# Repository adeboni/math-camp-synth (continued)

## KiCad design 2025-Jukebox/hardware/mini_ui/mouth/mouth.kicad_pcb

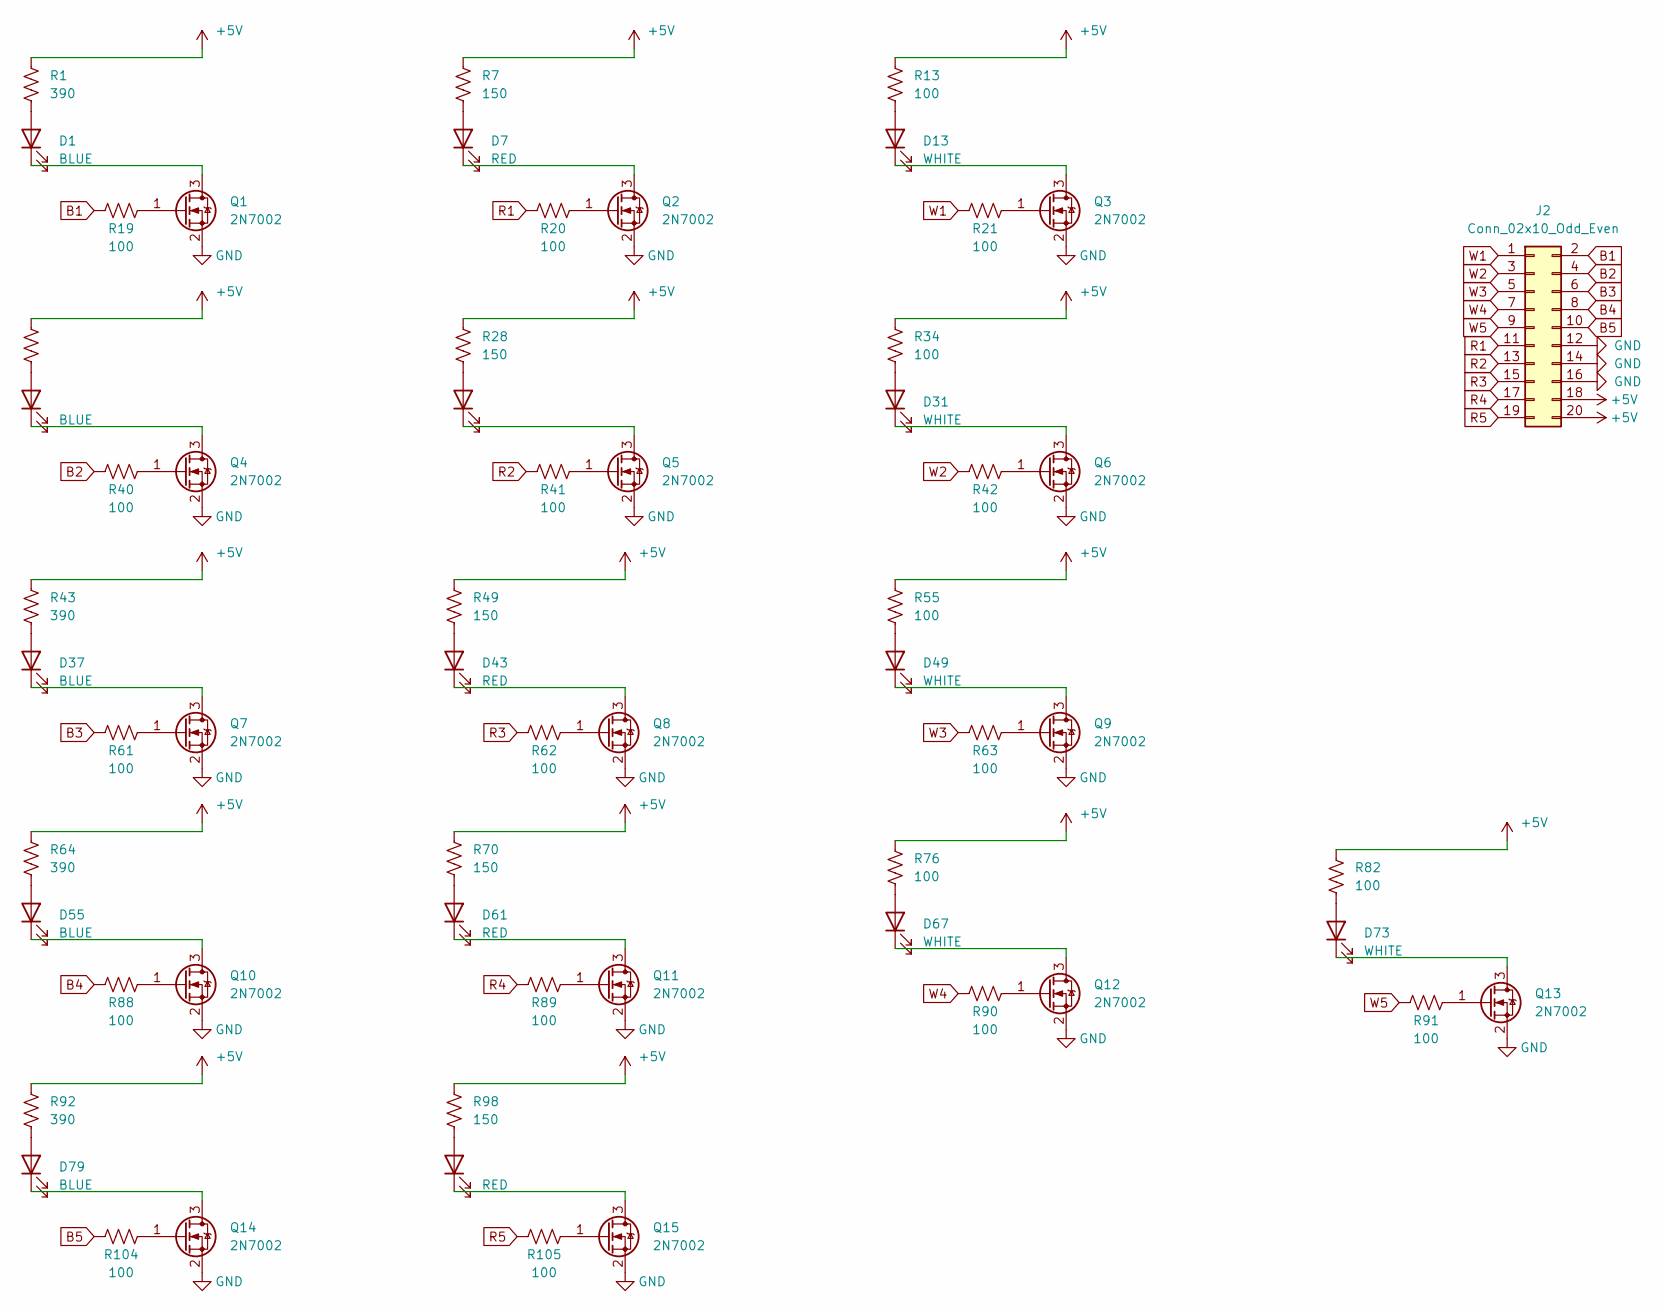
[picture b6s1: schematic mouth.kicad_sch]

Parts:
D1, D19, D37, D55, D79: BLUE; LED_0603_1608Metric
D7, D25, D43, D61, D85: RED; LED_0603_1608Metric
D13, D31, D49, D67, D73: WHITE; LED_0603_1608Metric
J2: Conn_02x10_Odd_Even; PinSocket_2x10_P2.54mm_Vertical_SMD
Q1, Q2, Q3, Q4, Q5, Q6, Q7, Q8, Q9, Q10, Q11, Q12, Q13, Q14, Q15: 2N7002; SOT-23
R1, R22, R43, R64, R92: 390; R_0603_1608Metric
R7, R28, R49, R70, R98: 150; R_0603_1608Metric
R13, R19, R20, R21, R34, R40, R41, R42, R55, R61, R62, R63, R76, R82, R88, R89, R90, R91, R104, R105: 100; R_0603_1608Metric

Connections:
+5V: J2.18, J2.20, R1.2, R7.2, R13.2, R22.2, R28.2, R34.2, R43.2, R49.2, R55.2, R64.2, R70.2, R76.2, R82.2, R92.2, R98.2
B1: J2.2, R19.1
B2: J2.4, R40.1
B3: J2.6, R61.1
B4: J2.8, R88.1
B5: J2.10, R104.1
GND: J2.12, J2.14, J2.16, Q1.2 (S), Q2.2 (S), Q3.2 (S), Q4.2 (S), Q5.2 (S), Q6.2 (S), Q7.2 (S), Q8.2 (S), Q9.2 (S), Q10.2 (S), Q11.2 (S), Q12.2 (S), Q13.2 (S), Q14.2 (S), Q15.2 (S)
unnamed: D1.2 (A), R1.1
unnamed: D1.1 (K), Q1.3 (D)
unnamed: D7.2 (A), R7.1
unnamed: D7.1 (K), Q2.3 (D)
unnamed: D13.2 (A), R13.1
unnamed: D13.1 (K), Q3.3 (D)
unnamed: D19.2 (A), R22.1
unnamed: D19.1 (K), Q4.3 (D)
unnamed: D25.2 (A), R28.1
unnamed: D25.1 (K), Q5.3 (D)
unnamed: D31.2 (A), R34.1
unnamed: D31.1 (K), Q6.3 (D)
unnamed: D37.2 (A), R43.1
unnamed: D37.1 (K), Q7.3 (D)
unnamed: D43.2 (A), R49.1
unnamed: D43.1 (K), Q8.3 (D)
unnamed: D49.2 (A), R55.1
unnamed: D49.1 (K), Q9.3 (D)
unnamed: D55.2 (A), R64.1
unnamed: D55.1 (K), Q10.3 (D)
unnamed: D61.2 (A), R70.1
unnamed: D61.1 (K), Q11.3 (D)
unnamed: D67.2 (A), R76.1
unnamed: D67.1 (K), Q12.3 (D)
unnamed: D73.2 (A), R82.1
unnamed: D73.1 (K), Q13.3 (D)
unnamed: D79.2 (A), R92.1
unnamed: D79.1 (K), Q14.3 (D)
unnamed: D85.2 (A), R98.1
unnamed: D85.1 (K), Q15.3 (D)
unnamed: Q1.1 (G), R19.2
unnamed: Q2.1 (G), R20.2
unnamed: Q3.1 (G), R21.2
unnamed: Q4.1 (G), R40.2
unnamed: Q5.1 (G), R41.2
unnamed: Q6.1 (G), R42.2
unnamed: Q7.1 (G), R61.2
unnamed: Q8.1 (G), R62.2
unnamed: Q9.1 (G), R63.2
unnamed: Q10.1 (G), R88.2
unnamed: Q11.1 (G), R89.2
unnamed: Q12.1 (G), R90.2
unnamed: Q13.1 (G), R91.2
unnamed: Q14.1 (G), R104.2
unnamed: Q15.1 (G), R105.2
R1: J2.11, R20.1
R2: J2.13, R41.1
R3: J2.15, R62.1
R4: J2.17, R89.1
R5: J2.19, R105.1
W1: J2.1, R21.1
W2: J2.3, R42.1
W3: J2.5, R63.1
W4: J2.7, R90.1
W5: J2.9, R91.1

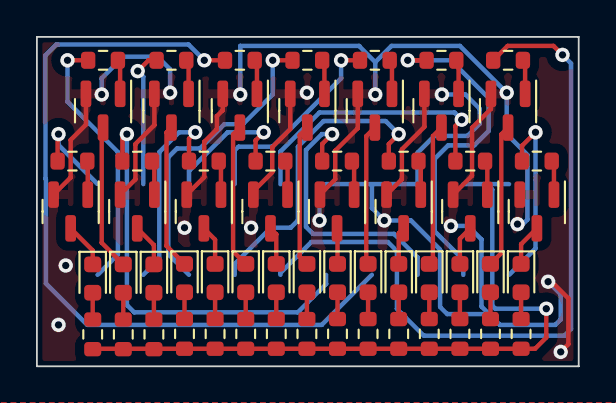
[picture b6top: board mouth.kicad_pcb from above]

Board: 2 copper layers, 30.1 x 18.3 mm, 61 parts (1 on the bottom side), 62 nets.

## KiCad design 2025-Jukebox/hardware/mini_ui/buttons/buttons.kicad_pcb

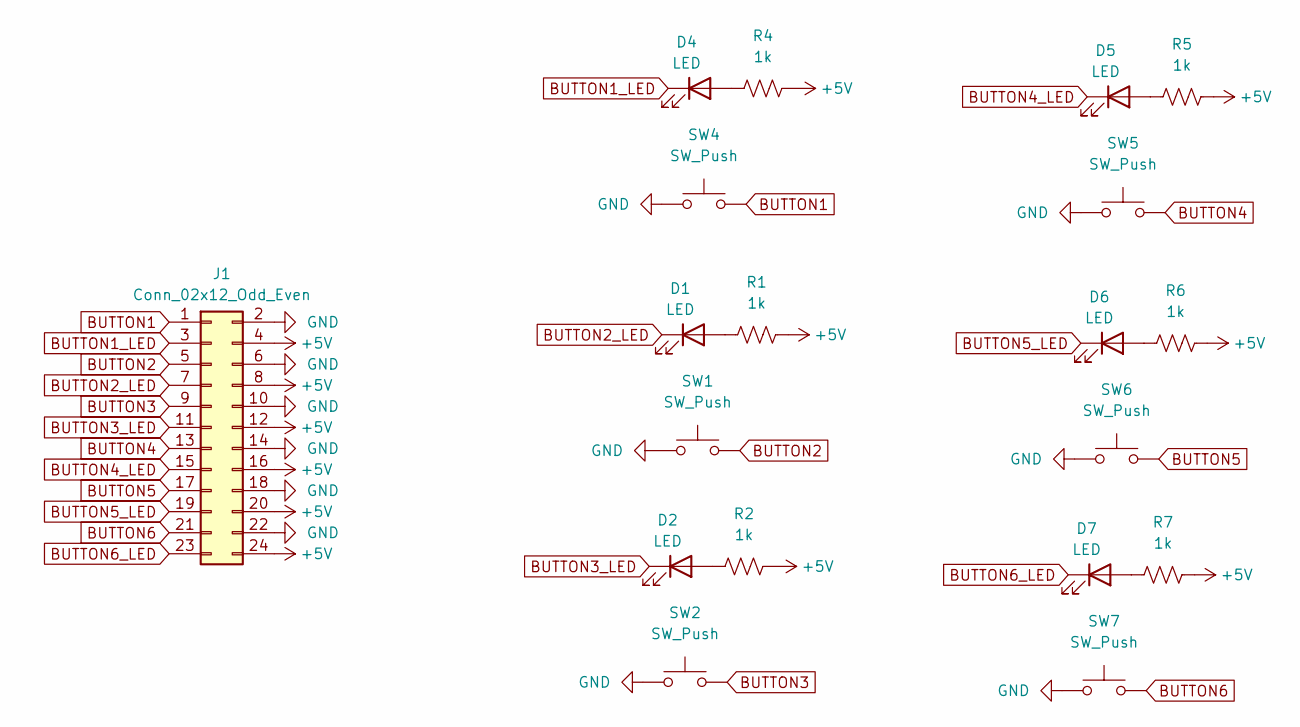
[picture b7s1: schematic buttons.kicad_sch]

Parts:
D1, D2, D4, D5, D6, D7: LED; LED_0603_1608Metric
J1: Conn_02x12_Odd_Even; PinSocket_2x12_P2.54mm_Vertical_SMD
R1, R2, R4, R5, R6, R7: 1k; R_0603_1608Metric
SW1, SW2, SW4, SW5, SW6, SW7: SW_Push; SW_Push_SPST_NO_Alps_SKRK

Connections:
+5V: J1.4, J1.8, J1.12, J1.16, J1.20, J1.24, R1.2, R2.2, R4.2, R5.2, R6.2, R7.2
BUTTON1: J1.1, SW4.2
BUTTON1_LED: D4.1 (K), J1.3
BUTTON2: J1.5, SW1.2
BUTTON2_LED: D1.1 (K), J1.7
BUTTON3: J1.9, SW2.2
BUTTON3_LED: D2.1 (K), J1.11
BUTTON4: J1.13, SW5.2
BUTTON4_LED: D5.1 (K), J1.15
BUTTON5: J1.17, SW6.2
BUTTON5_LED: D6.1 (K), J1.19
BUTTON6: J1.21, SW7.2
BUTTON6_LED: D7.1 (K), J1.23
GND: J1.2, J1.6, J1.10, J1.14, J1.18, J1.22, SW1.1, SW2.1, SW4.1, SW5.1, SW6.1, SW7.1
unnamed: D1.2 (A), R1.1
unnamed: D2.2 (A), R2.1
unnamed: D4.2 (A), R4.1
unnamed: D5.2 (A), R5.1
unnamed: D6.2 (A), R6.1
unnamed: D7.2 (A), R7.1

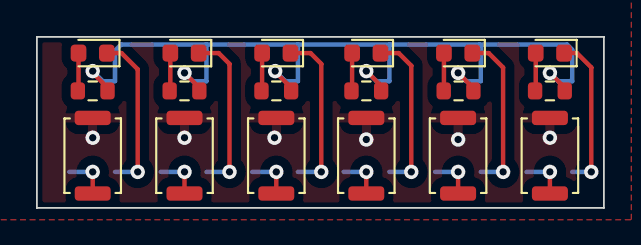
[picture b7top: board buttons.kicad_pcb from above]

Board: 2 copper layers, 31.5 x 9.5 mm, 19 parts (1 on the bottom side), 20 nets.

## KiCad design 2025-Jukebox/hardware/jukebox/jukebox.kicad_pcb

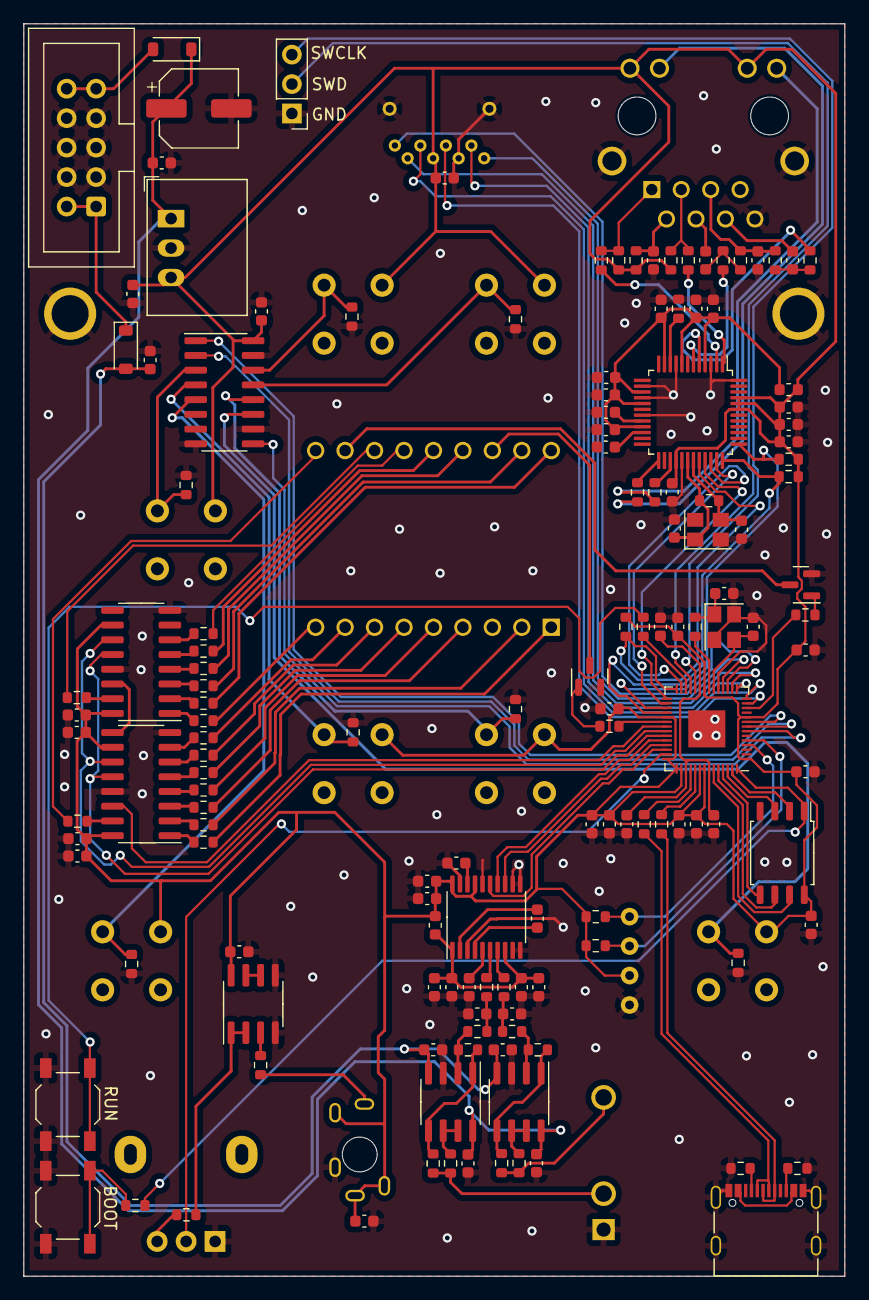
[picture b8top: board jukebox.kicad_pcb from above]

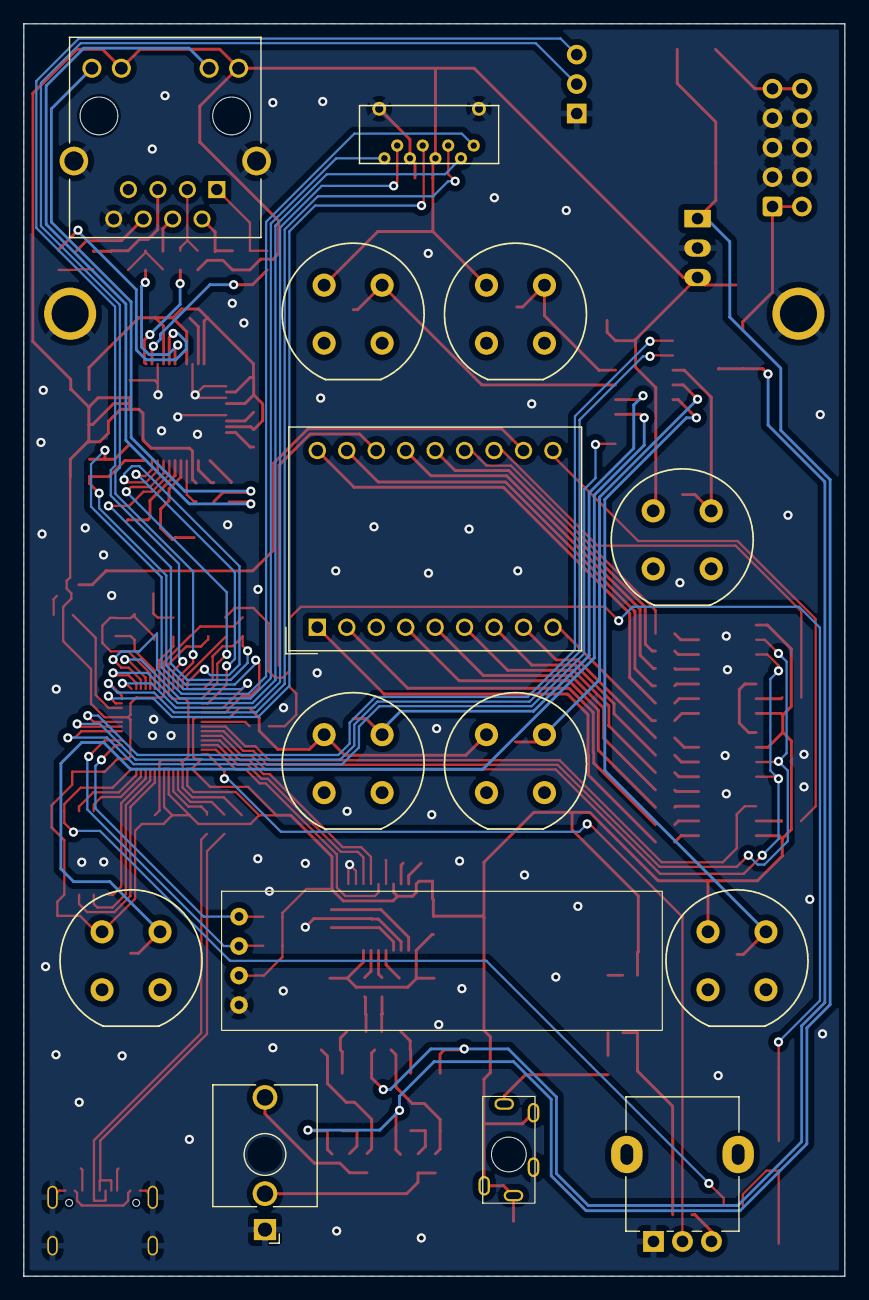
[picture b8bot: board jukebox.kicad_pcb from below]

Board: 2 copper layers, 70.8 x 108.0 mm, 160 parts (14 on the bottom side), 140 nets.

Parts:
C1, C2, C3, C4, C5, C6, C7, C8, C9, C13, C14, C15, C16, C17, C18, C19, C20, C21, C22, C23, C27, C31, C38, C40, C45, C46, C53, C54, C55, C56, C57, C59: 100n; C_0603_1608Metric
C10, C11, C44: 1u; C_0603_1608Metric
C12, C30, C36, C37, C39, C41, C42, C47, C48, C52, C58: 10u; C_0603_1608Metric
C24, C28: 27p; C_0603_1608Metric
C25, C29: 22p; C_0603_1608Metric
C26, C32: 10n; C_0603_1608Metric
C33, C34: 6.8n; C_0603_1608Metric
C35: 100u; CP_Elec_6.3x5.4
C43, C49: 2.2u; C_0603_1608Metric
C50, C51: 2.2n; C_0603_1608Metric
D1, D2: SM4007; D_SOD-123
FB1, FB3: FerriteBead; L_0603_1608Metric
H1, H2: MountingHole_Pad; MountingHole_3.2mm_M3_DIN965_Pad
J1: AudioJack3_SwitchTR; STX-3790-5N
J2: USB_C_Receptacle_USB2.0; USB_C_Receptacle_Palconn_UTC16-G
J3: AudioJack2_SwitchT; Jack_3.5mm_QingPu_WQP-PJ398SM_Vertical_CircularHoles
J4: SI-46001-F; BEL_SI-46001-F
J5: Conn_01x04; SSD1306
J6: Conn_02x05_Odd_Even; IDC-Header_2x05_P2.54mm_Vertical
J7: Conn_01x03; PinHeader_1x03_P2.54mm_Vertical
Q1, Q2: MMBT3904; SOT-23
R1, R2, R24, R25, R38: 1k; R_0603_1608Metric
R3, R6, R13, R17, R18, R28, R31, R32, R33, R35, R36, R37, R39, R40, R41, R58: 100; R_0603_1608Metric
R4, R5: 27; R_0603_1608Metric
R7, R10, R59, R61: 5.1k; R_0603_1608Metric
R8, R14, R16, R43, R44, R45, R46, R47, R48, R49, R50, R51, R54, R55: 10k; R_0603_1608Metric
R9, R11, R12, R15: 4.7; R_0603_1608Metric
R19, R20, R21, R22: 49.9; R_0603_1608Metric
R23: 1M; R_0603_1608Metric
R26, R27, R34, R42: 470; R_0603_1608Metric
R29: 12.4k; R_0603_1608Metric
R30: 10; R_0603_1608Metric
R52, R53, R56, R57: 75; R_0603_1608Metric
R60: 100k; R_0603_1608Metric
RV1: 100k; Potentiometer_Alpha_RD901F-40-00D_Single_Vertical
SW1, SW2: SW_Push; SW_SPST_TL3342
SW3, SW4, SW5, SW6, SW7, SW8, SW9: SW_Push; Push_E-Switch_KS01Q01
U1: PCM5100A; TSSOP-20_4.4x6.5mm_P0.65mm
U2: RP2040; QFN-56-1EP_7x7mm_P0.4mm_EP3.2x3.2mm
U3: W5500; LQFP-48_7x7mm_P0.5mm
U4: PDC54-11GWA; DA56-11CGKWA
U5, U8: 74HC595; SOIC-16_3.9x9.9mm_P1.27mm
U6: R-783.3-1.0; Converter_DCDC_RECOM_R-78E-0.5_THT
U7: W25Q128JVS; SOIC-8_5.23x5.23mm_P1.27mm
U9: PJS008U-3000-0
U10, U11: NE5532; SOIC-8_3.9x4.9mm_P1.27mm
U12: MCP6002-xSN; SOIC-8_3.9x4.9mm_P1.27mm
U13: 74HC165; SOIC-16_3.9x9.9mm_P1.27mm
Y1: 12MHz; Crystal_SMD_3225-4Pin_3.2x2.5mm
Y2: 25MHz; Crystal_SMD_3225-4Pin_3.2x2.5mm

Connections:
+1V1: C1.1, C2.1, C10.1, U2.23 (DVDD), U2.45 (VREG_VOUT), U2.50 (DVDD)
+3.3V: C3.1, C4.1, C5.1, C6.1, C7.1, C8.1, C9.1, C11.1, C12.1, C13.1, C14.1, C15.1, C16.1, C23.1, C27.1, C36.1, C37.1, C38.1, C39.1, C40.1, C42.1, C57.1, C58.1, C59.1, FB1.1, FB3.1, J1.R, J1.RN, J1.TN, J4.10, J4.12, J5.3, R8.1, R14.1, R16.1, R19.2, R20.2, R30.2, R59.2, R61.2, SW3.1, SW4.1, SW5.1, SW6.1, SW7.1, SW8.1, SW9.1, U1.17 (XSMT), U1.20 (DVDD), U2.1 (IOVDD), U2.10 (IOVDD), U2.22 (IOVDD), U2.33 (IOVDD), U2.42 (IOVDD), U2.43 (ADC_AVDD), U2.44 (VREG_IN), U2.48 (USB_VDD), U2.49 (IOVDD), U3.28 (VDD), U3.43 (PMODE2), U3.44 (PMODE1), U3.45 (PMODE0), U5.10 (~SRCLR), U5.16 (VCC), U6.3 (OUT), U7.8 (VCC), U8.10 (~SRCLR), U8.16 (VCC), U9.P$4 (4_VDD), U12.8 (V+), U13.16 (VCC)
+3.3VA: C17.1, C18.1, C19.1, C20.1, C21.1, C22.1, FB1.2, U3.4 (AVDD), U3.8 (AVDD), U3.11 (AVDD), U3.15 (AVDD), U3.17 (AVDD), U3.21 (AVDD)
+12V: C35.1, C41.1, C53.1, C55.1, D2.1 (K), U6.1 (IN), U10.8 (V+), U11.8 (V+)
-12V: C52.1, C54.2, C56.2, D1.2 (A), U10.4 (V-), U11.4 (V-)
/CS_0: R8.2, U2.28 (GPIO17), U3.32 (~SCS)
/INTn: R14.2, U2.32 (GPIO21), U3.36 (~INT)
/MISO_0: U2.27 (GPIO16), U3.34 (MISO)
/MOSI_0: U2.30 (GPIO19), U3.35 (MOSI)
/QSPI_SCLK: U2.52 (QSPI_SCLK), U7.6 (CLK)
/QSPI_SD0: U2.53 (QSPI_SD0), U7.5 (DI(IO0))
/QSPI_SD1: U2.55 (QSPI_SD1), U7.2 (DO(IO1))
/QSPI_SD2: U2.54 (QSPI_SD2), U7.3 (IO2)
/QSPI_SD3: U2.51 (QSPI_SD3), U7.7 (IO3)
/QSPI_SS: R38.1, U2.56 (QSPI_SS), U7.1 (~CS)
/RSTn: R16.2, U2.31 (GPIO20), U3.37 (~RST)
/RUN: R25.1, U2.26 (RUN)
/SCK_0: U2.29 (GPIO18), U3.33 (SCLK)
/~USB_BOOT: R38.2, SW2.2
ACTn: R27.1, U3.27 (ACTLED)
BCK_PWM1: U1.13 (BCK), U2.39 (GPIO27_ADC1)
BTN_CP: U2.8 (GPIO6), U13.2 (CP)
BTN_PL: U2.9 (GPIO7), U13.1 (~PL)
BTN_Q7: U2.7 (GPIO5), U13.9 (Q7)
D+: J2.A6 (D+), J2.B6 (D+), R4.1
D-: J2.A7 (D-), J2.B7 (D-), R5.1
GND: C1.2, C2.2, C3.2, C4.2, C5.2, C6.2, C7.2, C8.2, C9.2, C10.2, C11.2, C12.2, C13.2, C14.2, C15.2, C16.2, C17.2, C18.2, C19.2, C20.2, C21.2, C22.2, C23.2, C24.2, C25.1, C26.1, C27.2, C28.2, C29.2, C30.2, C31.2, C32.1, C35.2, C36.2, C37.2, C38.2, C39.2, C40.2, C41.2, C42.2, C44.2, C45.2, C46.2, C47.2, C48.2, C49.2, C50.2, C51.1, C52.2, C53.2, C54.1, C55.2, C56.1, C57.2, C58.2, C59.2, H1.1, H2.1, J1.S, J2.A1 (GND), J2.A12 (GND), J2.B1 (GND), J2.B12 (GND), J2.S1 (SHIELD), J3.S, J4.8, J4.SH, J5.4, J6.3, J6.4, J6.5, J6.6, J6.7, J6.8, J7.1, Q1.2 (E), Q2.2 (E), R7.1, R10.1, R29.1, R43.2, R44.2, R45.2, R46.2, R47.2, R48.2, R49.2, RV1.1, SW1.1, SW2.1, U1.3 (CPGND), U1.9 (AGND), U1.10 (DEMP), U1.11 (FLT), U1.12 (SCK), U1.16 (FMT), U1.19 (DGND), U2.19 (TESTEN), U2.57 (GND), U3.3 (AGND), U3.9 (AGND), U3.14 (AGND), U3.16 (AGND), U3.19 (AGND), U3.29 (GND), U3.48 (AGND), U5.8 (GND), U5.13 (~OE), U6.2 (GND), U7.4 (GND), U8.8 (GND), U8.13 (~OE), U9.P$6 (6_VSS/GND), U9.P$9 (HOUSING_1), U9.P$10 (HOUSING_2), U10.3 (+), U11.3 (+), U12.4 (V-), U12.5 (+), U13.8 (GND), U13.10 (DS), U13.15 (~CE), Y1.2, Y1.4, Y2.2, Y2.4
LINKn: R26.1, U3.25 (LINKLED)
LRCLK_PWM0: U1.15 (LRCK), U2.40 (GPIO28_ADC2)
NUM_A: R33.1, U4.12 (A)
NUM_B: R3.1, U4.10 (B)
NUM_C: R35.1, U4.9 (C)
NUM_D: R31.1, U4.7 (D)
NUM_DIG1: R1.2, U2.34 (GPIO22)
NUM_DIG2: R2.2, U2.12 (GPIO9)
NUM_DP: R32.1, U4.8 (DP)
NUM_E: R6.1, U4.1 (E)
NUM_EN: U2.37 (GPIO25), U5.12 (RCLK), U8.12 (RCLK)
NUM_F: R36.1, U4.18 (F)
NUM_G: R37.1, U4.17 (G)
NUM_H: R39.1, U4.15 (H)
NUM_J: R40.1, U4.14 (J)
NUM_K: R28.1, U4.6 (K)
NUM_L: R18.1, U4.5 (L)
NUM_M: R17.1, U4.4 (M)
NUM_N: R13.1, U4.2 (N)
NUM_P: R41.1, U4.13
NUM_SCK: U2.36 (GPIO24), U5.11 (SRCLK), U8.11 (SRCLK)
NUM_SER: U2.35 (GPIO23), U5.14 (SER)
unnamed: C28.1, R24.2, Y1.1
unnamed: C50.1, R42.2, R55.1
unnamed: C51.2, R34.2, R50.1
unnamed: D1.1 (K), J6.1, J6.2
unnamed: D2.2 (A), J6.9, J6.10
unnamed: J1.T, R60.1
unnamed: J2.A5 (CC1), R7.2
unnamed: J2.B5 (CC2), R10.2
unnamed: J2.A4 (VBUS), J2.A9 (VBUS), J2.B4 (VBUS), J2.B9 (VBUS)
unnamed: J3.T, R56.2, R57.2
unnamed: J3.TN, R52.2, R53.2
unnamed: J4.9, R27.2
unnamed: J4.11, R26.2
unnamed: C33.2, J4.4 (RD+)
unnamed: C34.1, J4.6 (RD-)
unnamed: C32.2, J4.2 (TCT), R30.1
unnamed: J7.2, U2.25 (SWD)
unnamed: J7.3, U2.24 (SWCLK)
unnamed: Q1.1 (B), R1.1
unnamed: Q1.3 (C), U4.16 (DIG_1)
unnamed: Q2.1 (B), R2.1
unnamed: Q2.3 (C), U4.11 (DIG_2)
unnamed: R25.2, SW1.2
unnamed: R58.2, RV1.3
unnamed: C43.2, U1.4 (CAPM)
unnamed: C43.1, U1.2 (CAPP)
unnamed: C44.1, U1.18 (LDOO)
unnamed: R34.1, U1.6 (OUTL)
unnamed: R42.1, U1.7 (OUTR)
unnamed: C49.1, U1.5 (VNEG)
unnamed: R5.2, U2.46 (USB_DM)
unnamed: R4.2, U2.47 (USB_DP)
unnamed: C24.1, U2.20 (XIN), Y1.3
unnamed: R24.1, U2.21 (XOUT)
unnamed: C31.1, U3.22 (1V2O)
unnamed: R29.2, U3.10 (EXRES1)
unnamed: R12.1, U3.5 (RXN)
unnamed: R15.2, U3.6 (RXP)
unnamed: C30.1, U3.20 (TOCAP)
unnamed: R9.1, U3.1 (TXN)
unnamed: R11.2, U3.2 (TXP)
unnamed: C25.2, R23.2, U3.30 (XI/CLKIN), Y2.1
unnamed: C29.1, R23.1, U3.31 (XO), Y2.3
unnamed: R3.2, U5.15 (QA)
unnamed: R6.2, U5.1 (QB)
unnamed: R13.2, U5.2 (QC)
unnamed: R17.2, U5.3 (QD)
unnamed: R18.2, U5.4 (QE)
unnamed: R28.2, U5.5 (QF)
unnamed: R31.2, U5.6 (QG)
unnamed: U5.9 (QH'), U8.14 (SER)
unnamed: R32.2, U5.7 (QH)
unnamed: R33.2, U8.15 (QA)
unnamed: R35.2, U8.1 (QB)
unnamed: R36.2, U8.2 (QC)
unnamed: R37.2, U8.3 (QD)
unnamed: R39.2, U8.4 (QE)
unnamed: R40.2, U8.5 (QF)
unnamed: R41.2, U8.6 (QG)
unnamed: R50.2, R51.1, U10.2 (-)
unnamed: R51.2, R53.1, U10.1, U10.5 (+)
unnamed: R52.1, U10.6 (-), U10.7
unnamed: R54.1, R55.2, U11.2 (-)
unnamed: R54.2, R57.1, U11.1, U11.5 (+)
unnamed: R56.1, U11.6 (-), U11.7
unnamed: R60.2, U12.3 (+)
unnamed: R58.1, U12.1, U12.2 (-)
unnamed: U12.6 (-), U12.7
unnamed: R49.1, SW3.2, U13.11 (D0)
unnamed: R48.1, SW6.2, U13.12 (D1)
unnamed: R47.1, SW4.2, U13.13 (D2)
unnamed: R46.1, SW5.2, U13.14 (D3)
unnamed: R45.1, SW8.2, U13.3 (D4)
unnamed: R44.1, SW7.2, U13.4 (D5)
unnamed: R43.1, SW9.2, U13.5 (D6)
PCM_DATA: U1.14 (DIN), U2.38 (GPIO26_ADC0)
RCT: C26.2, J4.5 (RCT), R21.2, R22.2
RXN: C34.2, R12.2, R21.1
RXP: C33.1, R15.1, R22.1
SCL: J5.2, R61.1, U2.5 (GPIO3)
SDA: J5.1, R59.1, U2.4 (GPIO2)
SD_CLK: U2.13 (GPIO10), U9.P$5 (5_CLK)
SD_CMD: U2.14 (GPIO11), U9.P$3 (3_CMD/DI)
SD_DAT0: U2.15 (GPIO12), U9.P$7 (7_DAT0/D0)
SD_DAT1: U2.18 (GPIO15), U9.P$8 (8_DAT1/X)
SD_DAT2: U2.17 (GPIO14), U9.P$1 (1_DAT2/X)
SD_DAT3: U2.16 (GPIO13), U9.P$2 (2_CD/DAT3/CS)
TXN: J4.3 (TD-), R9.2, R19.1
TXP: J4.1 (TD+), R11.1, R20.1
VOLUME: RV1.2, U2.41 (GPIO29_ADC3)
V_AUDIO: C45.1, C46.1, C47.1, C48.1, FB3.2, U1.1 (CPVDD), U1.8 (AVDD)

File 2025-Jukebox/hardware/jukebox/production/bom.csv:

Designator,Footprint,Quantity,Value,LCSC Part #
"C1, C13, C14, C15, C16, C17, C18, C19, C2, C20, C21, C22, C23, C27, C3, C31, C38, C4, C40, C45, C46, C5, C53, C54, C55, C56, C57, C59, C6, C7, C8, C9",0603,32,100n,C14663
"C10, C11, C44",0603,3,1u,C15849
"C12, C30, C36, C37, C39, C41, C42, C47, C48, C52, C58",0603,11,10u,C96446
"C24, C28",0603,2,27p,C1653
"C25, C29",0603,2,22p,C1653
"C26, C32",0603,2,10n,C57112
"C33, C34",0603,2,6.8n,C1631
C35,CP_Elec_6.3x5.4,1,100u,C180946
"C43, C49",0603,2,2.2u,C23630
"C50, C51",0603,2,2.2n,C1604
"D1, D2",D_SOD-123,2,SM4007,C64898
"FB1, FB3",0603,2,FerriteBead,C1002
J2,USB_C_Receptacle_Palconn_UTC16-G,1,USB_C_Receptacle_USB2.0,C709357
"Q1, Q2",SOT-23,2,MMBT3904,C20526
"R1, R2, R24, R25, R38",0603,5,1k,C21190
"R10, R59, R61, R7",0603,4,5.1k,C23186
"R11, R12, R15, R9",0603,4,4.7,C23164
"R13, R17, R18, R28, R3, R31, R32, R33, R35, R36, R37, R39, R40, R41, R58, R6",0603,16,100,C22775
"R14, R16, R43, R44, R45, R46, R47, R48, R49, R50, R51, R54, R55, R8",0603,14,10k,C25804
"R19, R20, R21, R22",0603,4,49.9,C23185
R23,0603,1,1M,C22935
"R26, R27, R34, R42",0603,4,470,C23179
R29,0603,1,12.4k,C22865
R30,0603,1,10,C22859
"R4, R5",0603,2,27,C25190
"R52, R53, R56, R57",0603,4,75,C4275
R60,0603,1,100k,C25803
"SW1, SW2",SW_SPST_TL3342,2,SW_Push,C318884
U1,TSSOP-20_4.4x6.5mm_P0.65mm,1,PCM5100A,C107671
"U10, U11",SOIC-8_3.9x4.9mm_P1.27mm,2,NE5532,C7426
U12,SOIC-8_3.9x4.9mm_P1.27mm,1,MCP6002-xSN,C7377
U13,SOIC-16_3.9x9.9mm_P1.27mm,1,74HC165,C5613
U2,QFN-56-1EP_7x7mm_P0.4mm_EP3.2x3.2mm,1,RP2040,C2040
U3,LQFP-48_7x7mm_P0.5mm,1,W5500,C32843
"U5, U8",SOIC-16_3.9x9.9mm_P1.27mm,2,74HC595,C5947
U7,SOIC-8_5.23x5.23mm_P1.27mm,1,W25Q128JVS,C97521
Y1,Crystal_SMD_3225-4Pin_3.2x2.5mm,1,12MHz,C9002
Y2,Crystal_SMD_3225-4Pin_3.2x2.5mm,1,25MHz,C9006

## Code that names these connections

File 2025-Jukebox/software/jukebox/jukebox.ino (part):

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
#define SDA_PIN       2
#define SCL_PIN       3
#define BTN_Q7_PIN    5
#define BTN_CP_PIN    6
#define BTN_PL_PIN    7
#define SD_CLK_PIN    10
#define SD_CMD_PIN    11
#define SD_DAT3_PIN   13
#define SD_DAT2_PIN   14
#define SD_DAT1_PIN   15
#define SD_DAT0_PIN   12
#define WIZ_MISO_PIN  16
#define WIZ_CS_PIN    17
#define WIZ_SCK_PIN   18
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bool displayUpdating = false;

uint16_t volumeRaw = 0;
float volume = 0;

File file;
AudioFileSourceSD *sdSource;
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  Wire1.setSCL(SCL_PIN);
  Wire1.begin();

  pinMode(BTN_PL_PIN, OUTPUT);
  pinMode(BTN_Q7_PIN, INPUT);
  pinMode(BTN_CP_PIN, OUTPUT);

  pinMode(WIZ_RST_PIN, OUTPUT);
  digitalWrite(WIZ_RST_PIN, LOW);
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  out->udpBuffer[0] = PACKET_ID_AUDIO_DATA;
  memset(out->udpBuffer + 1, 128, UDP_AUDIO_BUFF_SIZE - 1);

  SPI1.setRX(SD_DAT0_PIN);
  SPI1.setTX(SD_CMD_PIN);
  SPI1.setSCK(SD_CLK_PIN);
  SPI1.setCS(SD_DAT3_PIN);
  SD.begin(SD_DAT3_PIN, SPI_FULL_SPEED, SPI1);

  for (int i = 0; i < 260; i++)
    for (int j = 0; j < MAX_SONG_NAME_LEN; j++)
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void checkButtons() {
  static unsigned long lastButtonCheck = 0;
  if (millis() - lastButtonCheck > 50) {
    digitalWrite(BTN_PL_PIN, LOW);
    digitalWrite(BTN_PL_PIN, HIGH);

    for (int i = 0; i < 8; i++) {
      uint8_t buttonState = digitalRead(BTN_Q7_PIN);
      if (buttonState && !buttonStates[i])
        buttonAction(i);
      buttonStates[i] = buttonState;
      digitalWrite(BTN_CP_PIN, HIGH);
      digitalWrite(BTN_CP_PIN, LOW);
    }
    lastButtonCheck = millis();
  }
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
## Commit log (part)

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2022-08-22 initial upload
2022-12-08 Re-organized and added 2023 synth files
2022-12-08 Re-organized source code
2022-12-22 Added display adapter
2022-12-29 Added led meter and motor mount
2023-01-10 Re-organized files
2023-01-13 Added LED meter support
2023-01-23 minor bug fixes
2023-01-26 Revamped synth code
2023-07-27 Updated jukebox code
2023-07-27 Added new hardware
2023-07-30 Moved defines to another file
2023-07-30 Fixed occassional crashing when switching songs
2023-08-07 Added mode 2
2023-08-14 Finished mode 2
2023-08-14 Added power-off functionality
2023-08-21 Double animation times
2023-11-15 Updated to latest versions
2023-11-15 Added initial firmware
2023-11-15 Added wand and power supply files
2023-11-15 Added wand production files
2023-11-15 Changed 3.3v regulator
2023-11-17 Minor fixes
2023-11-17 Added a version of the wand with a mic
2023-11-17 Added decoupling cap to power supply toggle board
2023-11-19 Added power selection jumper for LED
2023-11-20 Updated power supply toggle pcb
2023-11-20 Simplified the MAX7313 code
2023-11-21 Added HID functionality
2023-11-22 Fixed HID issues
2023-11-22 Got sACN working
2023-11-22 Added LCD display code
2023-11-27 Added level shifters to LCD display signals
2023-11-27 Added rounded corners to power supply toggle PCB
2023-11-30 Fixed some LCD display bugs
2023-12-01 Updated schematic
2023-12-18 Added pi power board
2023-12-21 Added single board wand design
2023-12-21 Added some extra silkscreen indicators
2023-12-22 Updated wand PCBs
2023-12-22 Added 3D models
2023-12-27 Updated wand PCB
2024-01-04 Fixed wiring issue
2024-01-04 Updated gerbers
2024-01-05 Added neopixel boost converter board
2024-01-06 Updated wand firmware
2024-01-08 Minor updates to wand
2024-01-08 Updated wand code
2024-01-09 Renamed files
2024-01-26 Updates to neopixel circuit and ui board firmware
2024-01-30 Updated wand simulators
2024-02-06 Update wand speed calculation
2024-02-06 Added bongo test
2024-03-11 Optimized sACN code
2024-05-03 Made gatt version of the wand
2024-05-06 Updated pullup resistor values
2024-08-05 Added jukebox 2025 updates
2024-08-06 Added 2025 gerbers
2024-08-07 Added 2025 wand PCB design
2024-08-07 Added footprint for light pipe
2024-08-09 Replaced IMU with BNO055
2024-08-09 Added production files
2024-08-19 Changed button location
2024-10-01 Wand bug fixes
2024-10-02 Switched to TCP
2024-10-02 Added python client code
2024-10-03 Wand TCP bug fixes
2024-10-03 Updated packet format
2024-10-04 Added audio packet transitions
2024-10-07 Added test version of wand code
2024-10-08 Minor improvements
2024-10-09 Added UDP version of wand code
2024-10-09 Bug fixes
2024-11-11 Added new UI board firmware
2024-11-26 Added new PCBs
2024-12-11 Added mini tester UI
2024-12-11 Added jukebox firmware
2024-12-11 Jukebox bug fixes
2024-12-19 Added song pause functionality
2024-12-19 Reverted song pause feature
2025-01-12 Added ui_module
2025-01-13 Added UI features
2025-01-13 Added wand receiver firmware
2025-01-14 Display update fix
2025-01-15 Added wand code
2025-01-16 SPI bug fixes
2025-01-17 More SPI work
2025-01-21 Added animation support
2025-01-21 Added morse code support
2025-01-22 Added sound effects
2025-01-23 Added basic laser functionality
2025-01-24 Added support for three lasers
2025-01-25 Optimizations
2025-01-27 Added spirograph animation
2025-01-27 Added wand functionality
2025-01-28 Added bubble animation
2025-01-29 Added pong mode
2025-01-29 Minor additions
2025-01-29 Audio buffer fixes
2025-01-29 Audio viz fixes
2025-01-30 Add pong sound effect support
2025-01-30 Added equation support
2025-01-31 Updated xy_t struct
2025-02-03 Animation updates
2025-02-03 Commented out unused graphics
2025-02-03 Added wand rotation color
2025-02-03 Optimized audio visualizer
2025-02-04 Added sd card setup scripts
2025-02-04 Wand drawing fixes
2025-02-04 Wand math updates
2025-02-04 Updated ESP32 I2S driver
2025-02-05 Updated audio visualization
2025-02-05 Audio visualizer bug fixes
2025-02-06 Minor refactoring
2025-02-06 Optimized wand calibration
2025-02-06 Code cleanup
2025-03-03 Added button cable adapter
2025-06-17 Added all animation mode
2025-06-22 Changed animation lengths
